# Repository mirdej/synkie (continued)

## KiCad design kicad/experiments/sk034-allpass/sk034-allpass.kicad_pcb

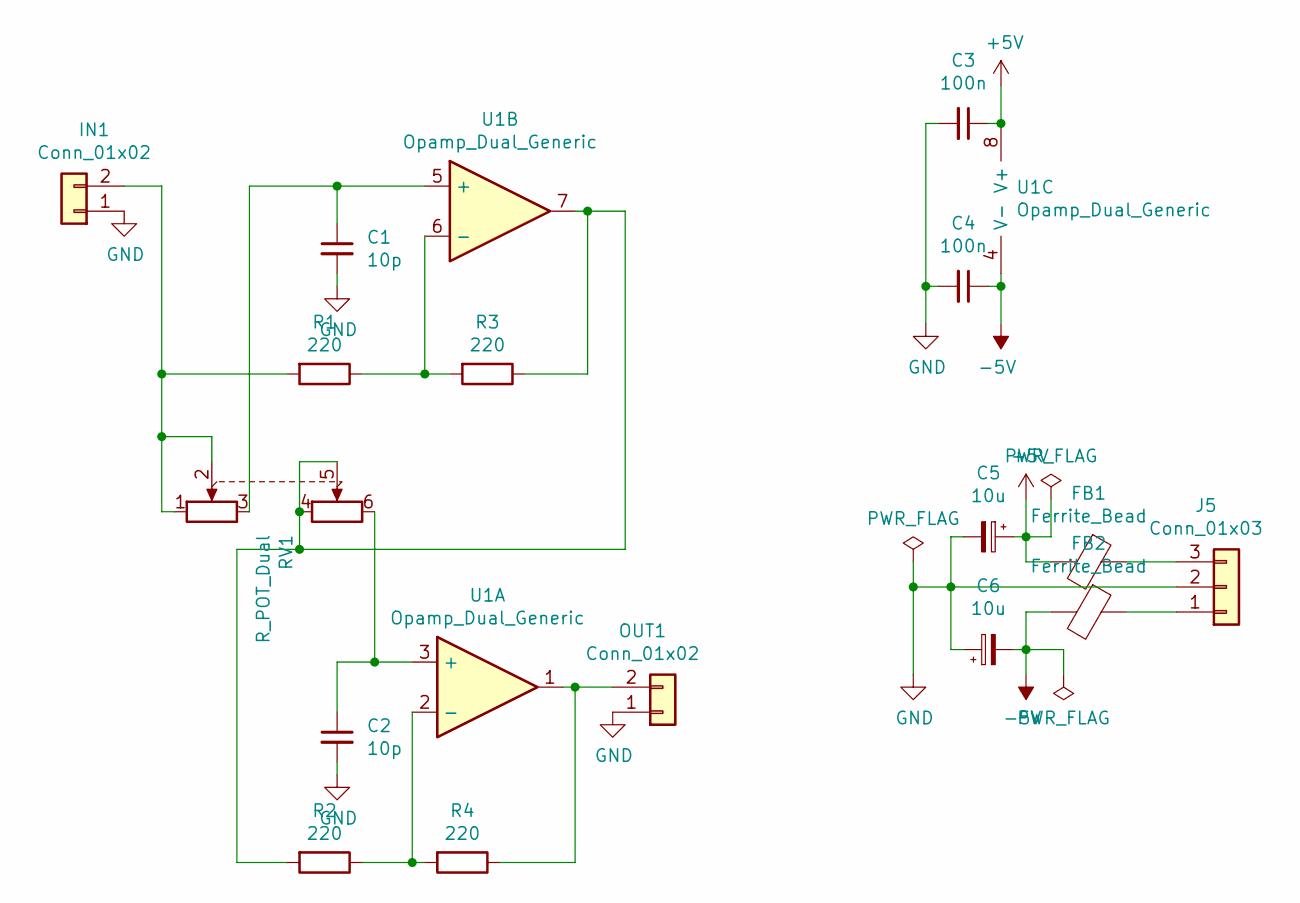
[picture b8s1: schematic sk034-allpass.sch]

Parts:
C1, C2: 10p; C_0805_2012Metric_Pad1.15x1.40mm_HandSolder
C3, C4: 100n; C_0603_1608Metric_Pad1.05x0.95mm_HandSolder
C5, C6: 10u; CP_EIA-3528-21_Kemet-B_Pad1.50x2.35mm_HandSolder
FB1, FB2: Ferrite_Bead; L_0805_2012Metric_Pad1.15x1.40mm_HandSolder
IN1: Conn_01x02; Molex_KK-254_AE-6410-02A_1x02_P2.54mm_Vertical
J5: Conn_01x03; Molex_KK-254_AE-6410-03A_1x03_P2.54mm_Vertical
OUT1: Conn_01x02; Molex_KK-254_AE-6410-02A_1x02_P2.54mm_Vertical
R1, R2, R3, R4: 220; R_0805_2012Metric_Pad1.15x1.40mm_HandSolder
RV1: R_POT_Dual; RK12L123
U1: Opamp_Dual_Generic; SOIC-8_3.9x4.9mm_P1.27mm

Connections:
+5V: C3.1, C5.1, FB1.2, U1.8 (V+)
-5V: C4.1, C6.2, FB2.2, U1.4 (V-)
GND: C1.2, C2.2, C3.2, C4.2, C5.2, C6.1, IN1.1, J5.2, OUT1.1
unnamed: C1.1, RV1.3, U1.5 (+)
unnamed: C2.1, RV1.6, U1.3 (+)
unnamed: FB1.1, J5.3
unnamed: FB2.1, J5.1
unnamed: IN1.2, R1.2, RV1.1, RV1.2
unnamed: OUT1.2, R4.1, U1.1
unnamed: R1.1, R3.2, U1.6 (-)
unnamed: R2.1, R4.2, U1.2 (-)
unnamed: R2.2, R3.1, RV1.4, RV1.5, U1.7

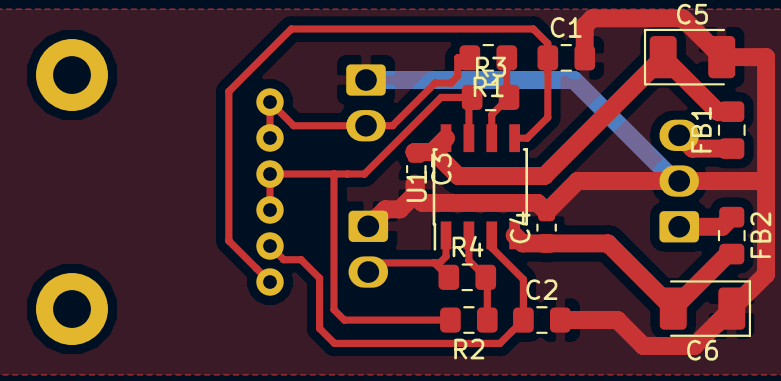
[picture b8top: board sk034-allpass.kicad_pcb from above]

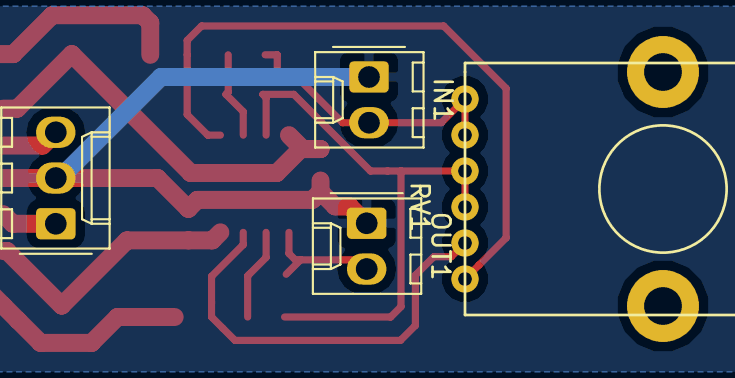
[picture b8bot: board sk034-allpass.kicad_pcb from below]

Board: 2 copper layers, 17 parts (4 on the bottom side), 12 nets.
